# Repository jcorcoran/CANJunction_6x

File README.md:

# CANJunction_6x
PCB project to aid CAN wire distribution. A 6x device version of https://github.com/jcorcoran/CANJunction

This PCB can be ordered from any fab house using the files in the [gerbers](gerbers) directory of this repository, including [oshpark](https://oshpark.com/shared_projects/lZ9DFcMB).  

Apply a piece of electrical or kaptop tape to the bottom of the PCB if it is going to be mounted diretly to a conductive surface.

## Parts:

The PCB uses push to connect terminal blocks. The part footprint is designed to allow any style connector that's typically found in this spacing.

We tend to use the Combicon PTSA family of [pheonix contacts](https://www.digikey.com/short/zdrh8825) ordering yellow and green pairs and then manually assemble them in alternating colors. Works with stripped wire (no connector/ferrule required) 16-24 awg.  
These connectors are also typically stocked at mouser. They can also be had from ebay/[aliexpress](https://www.aliexpress.com/item/32880938989.html). We haven't had problems with the off-brand ones, but YMMV.

## CAD

A step model of the PCB is [here](cad/)

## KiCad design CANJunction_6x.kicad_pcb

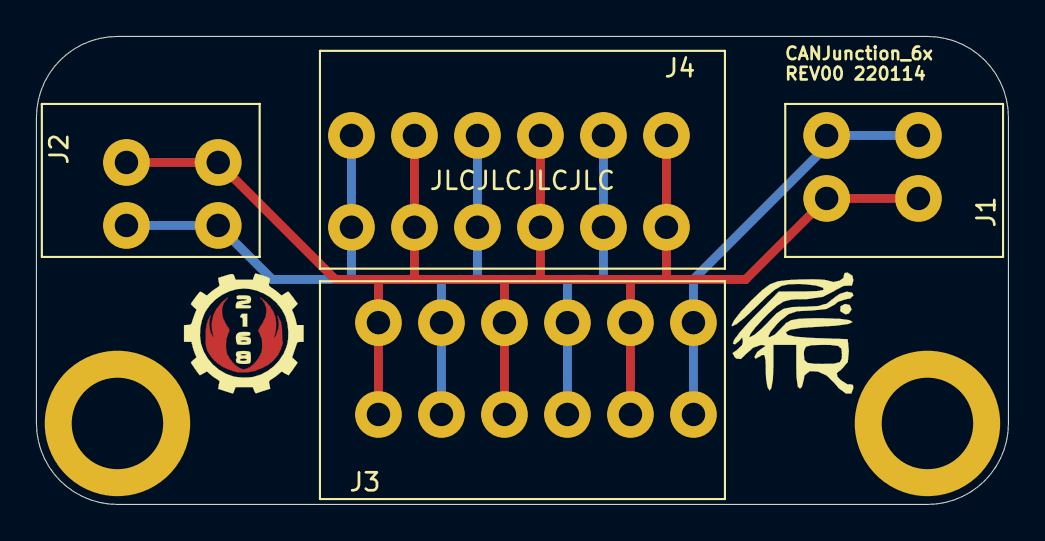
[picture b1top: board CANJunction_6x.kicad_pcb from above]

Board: 2 copper layers, 54.0 x 26.0 mm, 7 parts (0 on the bottom side), 2 nets.

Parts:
H1: Mechanical_MountingHole; mounting_holes
J1, J2: Connector_Screw_Terminal_01x02; TerminalBlock_Spring_2Pos_3.5mm
J3, J4: Connector_Screw_Terminal_01x06; TerminalBlock_Spring_6Pos_3.5mm
Wings: LOGO; gear_small_wings-f.mask
Wings#2: LOGO; gear_small_wings-cu

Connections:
unnamed: J1.1, J2.1, J3.1, J3.3, J3.5, J4.1, J4.3, J4.5
unnamed: J1.2, J2.2, J3.2, J3.4, J3.6, J4.2, J4.4, J4.6

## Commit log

2022-01-14 add images and readme
2022-02-07 add 4481 photo
2022-02-07 Create LICENSE
